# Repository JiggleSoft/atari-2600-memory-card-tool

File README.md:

# JiggleSoft's Atari 2600

## Memory Card USB Interface - Hardware, Firmware, and Software.

### Introduction

This repository contains the design and implementation details of a USB interface and software management tool for Atari 2600/7800 memory cards, namely the SaveKey and SaveKey+.

The aim of this project is to provide the cheapest and simplest complete management solution for Atari 2600/7800 memory cards (SaveKey) devices.

### Status

I am currently awaiting delivery of Microchip PIC MCU and Microchip Serial EEPROM integrated circuits, but there is a long lead time.
In the meantime work will proceed on soldering a USB Interface Tool development stripboard PCB and a savekey plus test device stripboard PCB.
Then software development will continue.

### Project Index

| Location                  | Description                                                                |
|---------------------------|----------------------------------------------------------------------------|
| memory-card-tool/hardware | USB interface's hardware design and implementation: Schematic, PCB, Notes. |
| memory-card-tool/firmware | USB interface's firmware source code.                                      |
| memory-card-tool/software | Memory Card management tool software for Linux and Windows.                |
| savekey-plus-test-device  | SaveKey+ test device's hardware design and implementation: Schematic, PCB (stripboard), Notes. |

*Note: that this repository will only be updated with content as specific milestones are reached.*
*The development is in progress and currently housed in a separate private repository.*

### Hardware

### Software

### SaveKey Plus Test Device

[SaveKey Plus Test Device Schematic](savekey-plus-test-device/hardware/kicad/savekey-plus-test-device/savekey-plus-test-device-schematic.pdf "SaveKey Plus Test Device Schematic")

### Licensing

Copyright (C) 2022 Justin Lane
All rights reserved.

*Note: A more applicable open license will be chosen in the future.*

### Contact Us

Please email atari2600@jigglesoft.co.uk regarding this repository.

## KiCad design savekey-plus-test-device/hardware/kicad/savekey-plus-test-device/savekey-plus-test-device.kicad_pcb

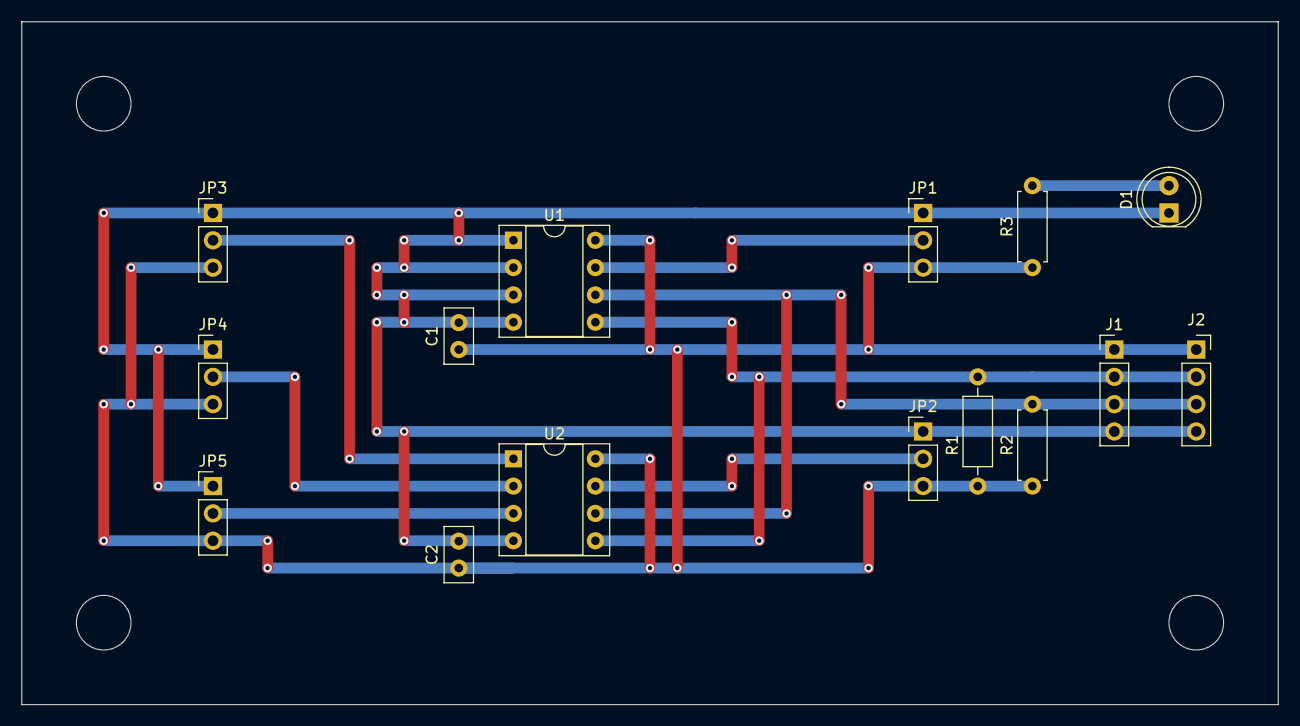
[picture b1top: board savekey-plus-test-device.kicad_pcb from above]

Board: 2 copper layers, 116.8 x 63.5 mm, 15 parts (0 on the bottom side), 10 nets.

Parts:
C1, C2: 0.1uF; C_Disc_D5.0mm_W2.5mm_P2.50mm
D1: LED; LED_D5.0mm
J1: Conn_01x04_Male; PinHeader_1x04_P2.54mm_Vertical
J2: Conn_01x04_Female; PinSocket_1x04_P2.54mm_Vertical
JP1, JP2, JP3, JP4, JP5: Jumper_3_Bridged12; PinHeader_1x03_P2.54mm_Vertical
R1: 10K; R_Axial_DIN0207_L6.3mm_D2.5mm_P10.16mm_Horizontal
R2: 10K; R_Axial_DIN0207_L6.3mm_D2.5mm_P7.62mm_Horizontal
R3: 1K; R_Axial_DIN0207_L6.3mm_D2.5mm_P7.62mm_Horizontal
U1, U2: 24LC256; DIP-8_W7.62mm_Socket

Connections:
+5V: C1.1, C2.1, J1.1, J2.1, JP1.3, JP2.3, JP3.3, JP4.3, JP5.3, R1.1, R2.1, R3.1, U1.8, U2.8
/SCL: J1.3, J2.3, R2.2, U1.6, U2.6
/SDA: J1.2, J2.2, R1.2, U1.5, U2.5
GND: C1.2, C2.2, D1.1, J1.4, J2.4, JP1.1, JP2.1, JP3.1, JP4.1, JP5.1, U1.1, U1.2, U1.3, U1.4, U2.4
unnamed: D1.2, R3.2
unnamed: JP1.2, U1.7
unnamed: JP2.2, U2.7
unnamed: JP3.2, U2.1
unnamed: JP4.2, U2.2
unnamed: JP5.2, U2.3

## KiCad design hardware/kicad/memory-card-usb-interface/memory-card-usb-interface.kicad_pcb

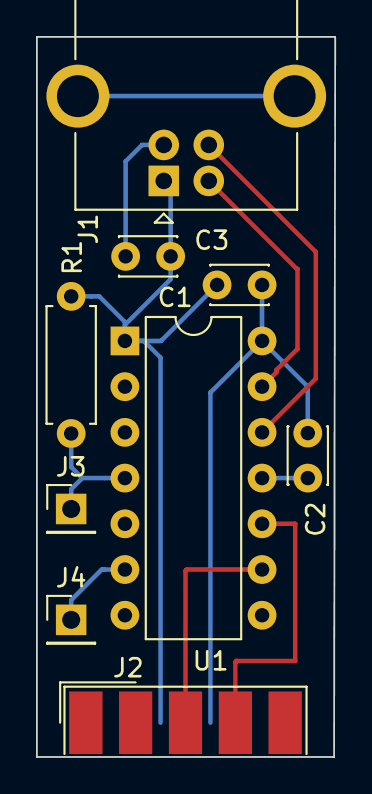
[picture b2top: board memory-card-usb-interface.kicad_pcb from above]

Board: 2 copper layers, 16.6 x 40.0 mm, 9 parts (0 on the bottom side), 9 nets.

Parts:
C1: 100nF; C_Disc_D3.0mm_W2.0mm_P2.50mm
C2: 470nF; C_Disc_D3.0mm_W2.0mm_P2.50mm
C3: 1uF; C_Disc_D3.0mm_W2.0mm_P2.50mm
J1: USB_B; USB_B_OST_USB-B1HSxx_Horizontal
J2: DB9_Male; DSUB-9_Male_EdgeMount_P2.77mm
J3: CONN_MCU_VPP; PinHeader_1x01_P2.54mm_Vertical
J4: CONN_MCU_LOG; PinHeader_1x01_P2.54mm_Vertical
R1: 10K; R_Axial_DIN0207_L6.3mm_D2.5mm_P7.62mm_Horizontal
U1: PIC16F1454-IP; DIP-14_W7.62mm

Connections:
/MCU_VDD: C1.1, C3.1, J1.1, J2.7, R1.1, U1.1
/MEM_SCL: J2.4, U1.10
/MEM_SDA: J2.3, U1.9
/USB_D+: J1.2, U1.13
/USB_D-: J1.3, U1.12
GNDPWR: C1.2, C2.2, C3.2, J1.4, J2.8, U1.14
unnamed: C2.1, U1.11
unnamed: J3.1, R1.2, U1.4
unnamed: J4.1, U1.6

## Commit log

2022-11-13 Initial commit of current LICENSE and README.md file. Also the initial hardware schematic and PCB design.
2022-11-21 Improvement to the schematic and PCB for available component dimensions and I2C pull-ups.
2022-11-22 Added stripboard DIY/Development version of the USB interface. Added schematic for Save Key Plus Test Device (WIP).
2022-11-28 Added software screenshot that is WIP.
2023-01-10 Updated README.md file with status and Save Key Plus Test Device. Added Save Key Plus Test Device stripboard PCB design along with PDF and PNG images. Renamed Save Key Plus Test Device schematic PDF 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
